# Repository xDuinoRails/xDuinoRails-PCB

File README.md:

View this project on [CADLAB.io](https://cadlab.io/project/28657).

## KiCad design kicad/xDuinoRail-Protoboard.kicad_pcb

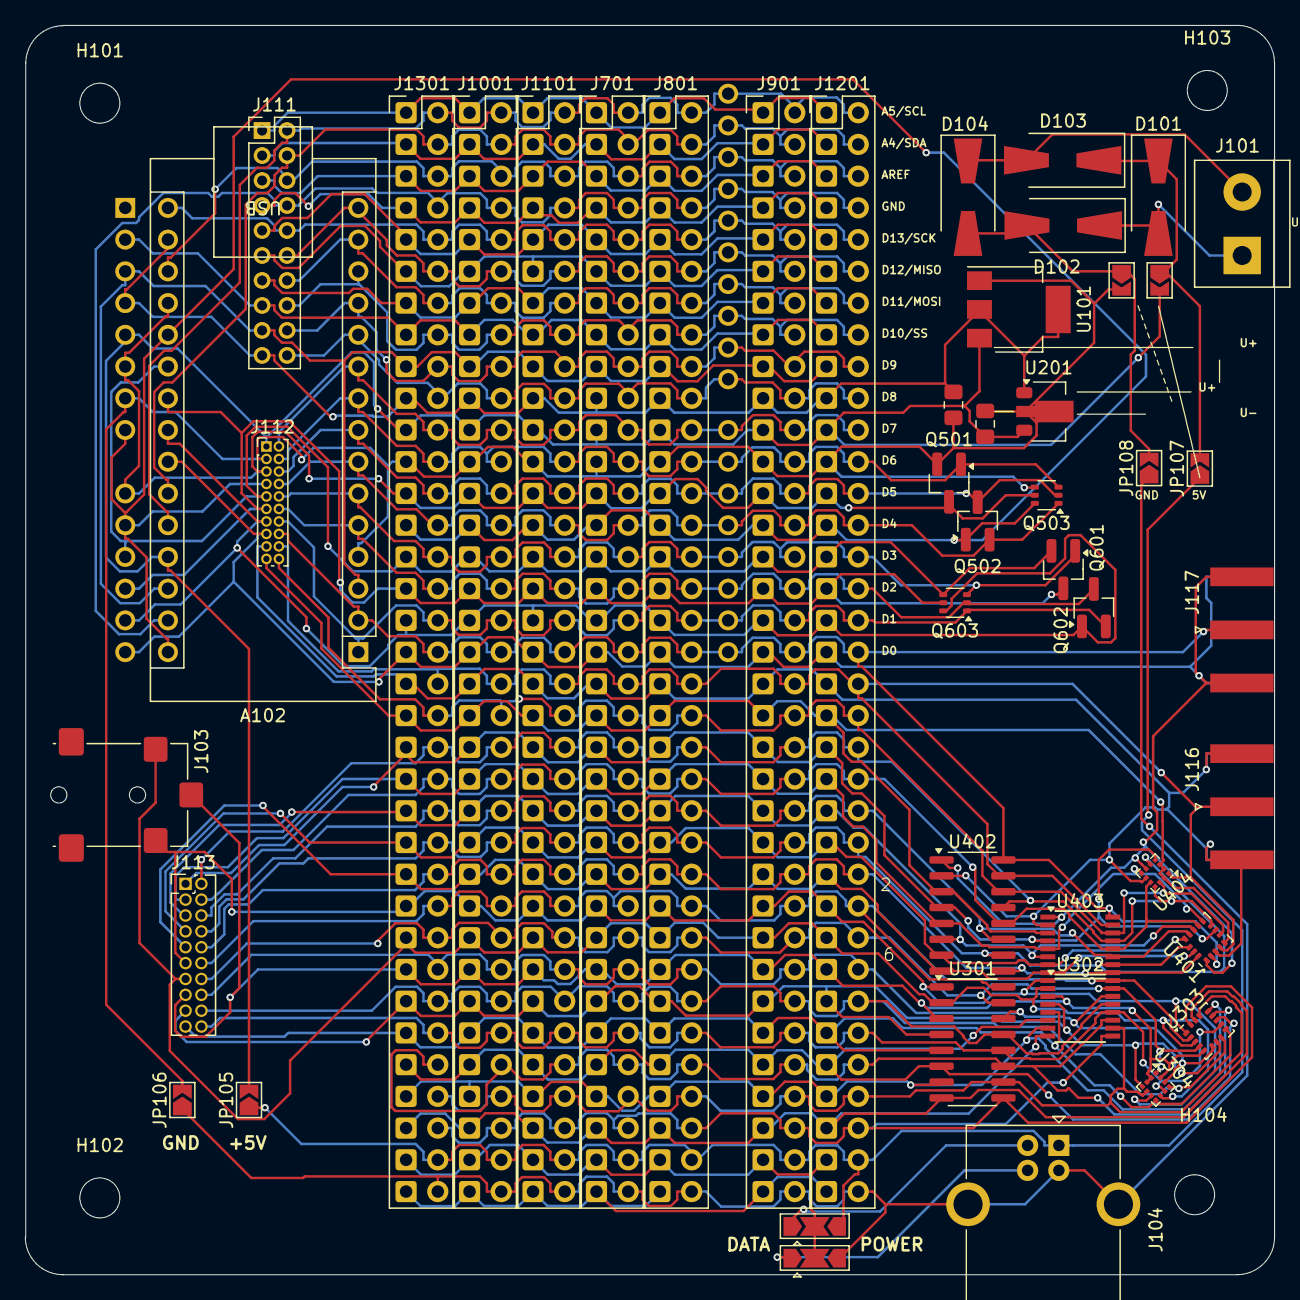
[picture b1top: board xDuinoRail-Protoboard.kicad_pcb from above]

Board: 2 copper layers, 100.0 x 100.0 mm, 51 parts (1 on the bottom side), 76 nets.

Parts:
A101: Arduino_UNO_R3
A102: Arduino_Nano_v3.x; Arduino_Nano
C201: 1uF; C_0805_2012Metric_Pad1.18x1.45mm_HandSolder
C202: 47uF; C_0805_2012Metric_Pad1.18x1.45mm_HandSolder
D101, D102, D103, D104: D; D_SMA-SMB_Universal_Handsoldering
H101, H102, H103, H104: MountingHole; MountingHole_3.2mm_M3
J101: Screw_Terminal_01x02; TerminalBlock_bornier-2_P5.08mm
J103: AudioJack3_Ground; Jack_3.5mm_Lumberg_1503_03_Horizontal
J104: USB_B; USB_B_OST_USB-B1HSxx_Horizontal
J111: Conn_02x10_Counter_Clockwise; PinHeader_2x10_P2.00mm_Vertical
J112: Conn_02x10_Counter_Clockwise; PinHeader_2x10_P1.00mm_Vertical
J113: Conn_02x10_Counter_Clockwise; PinHeader_2x10_P1.27mm_Vertical
J116, J117: Conn_Coaxial_Small; SMA_Amphenol_132289_EdgeMount
J701, J801, J901, J1001, J1101, J1201, J1301: Conn_02x35_Counter_Clockwise; PinHeader_2x35_P2.54mm_Vertical_Proto
JP103, JP104, JP105, JP106, JP107, JP108: SolderJumper_2_Open; SolderJumper-2_P1.3mm_Open_TrianglePad1.0x1.5mm
JP109, JP110: SolderJumper_3_Open; SolderJumper-3_P2.0mm_Open_TrianglePad1.0x1.5mm
Q501, Q502, Q601, Q602: 2N7002; SOT-23_Handsoldering
Q503, Q603: BC857BS; SOT-363_SC-70-6
U101: AMS1117-3.3; SOT-223-3_TabPin2
U201: HT7533-1; SOT-89-3
U301, U402: ULN2003; SOIC-16_3.9x9.9mm_P1.27mm
U302, U403: ULN2003; SSOP-16_3.9x4.9mm_P0.635mm
U303, U401: LIS3DH; LGA-16_3x3mm_P0.5mm_LayoutBorder3x5y
U304, U404: LIS3MDL; LGA-12_2x2mm_P0.5mm

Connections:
/AC0: D103.2 (A), D104.1 (K), J101.2
/AC1: D101.2 (A), D102.1 (K), J101.1
/Dm: J104.2 (D-), JP109.1 (A)
/Dp: J104.3 (D+), JP110.1 (A)
/L1: J111.1, J701.1, J801.1, J901.1, J1001.1, J1101.1, J1201.1, J1301.1
/L2: A101.32 (SCL/A5), A102.26 (A7), J111.2, J701.2, J801.2, J901.2, J1001.2, J1101.2, J1201.2, J1301.2
/L3: J111.3, J701.3, J801.3, J901.3, J1001.3, J1101.3, J1201.3, J1301.3
/L4: A101.31 (SDA/A4), A102.25 (A6), J111.4, J701.4, J801.4, J901.4, J1001.4, J1101.4, J1201.4, J1301.4
/L5: J111.5, J701.5, J801.5, J901.5, J1001.5, J1101.5, J1201.5, J1301.5
/L6: A101.30 (AREF), A102.18 (AREF), J111.6, J701.6, J801.6, J901.6, J1001.6, J1101.6, J1201.6, J1301.6
/L7: J111.7, J701.7, J801.7, J901.7, J1001.7, J1101.7, J1201.7, J1301.7
/L8: A101.29 (GND), A102.29 (GND), J111.8, J701.8, J801.8, J901.8, J1001.8, J1101.8, J1201.8, J1301.8
/L9: J111.9, J701.9, J801.9, J901.9, J1001.9, J1101.9, J1201.9, J1301.9
/L10: A101.28 (D13), A102.16 (D13), J111.10, J701.10, J801.10, J901.10, J1001.10, J1101.10, J1201.10, J1301.10
/L11: J111.11, J701.11, J801.11, J901.11, J1001.11, J1101.11, J1201.11, J1301.11
/L12: A101.27 (D12), A102.15 (D12), J111.12, J701.12, J801.12, J901.12, J1001.12, J1101.12, J1201.12, J1301.12
/L13: J111.13, J701.13, J801.13, J901.13, J1001.13, J1101.13, J1201.13, J1301.13
/L14: A101.26 (D11), A102.14 (D11), J111.14, J701.14, J801.14, J901.14, J1001.14, J1101.14, J1201.14, J1301.14
/L15: A101.2 (IOREF), J111.15, J701.15, J801.15, J901.15, J1001.15, J1101.15, J1201.15, J1301.15
/L16: A101.25 (D10), A102.13 (D10), J111.16, J701.16, J801.16, J901.16, J1001.16, J1101.16, J1201.16, J1301.16
/L17: A101.3 (~RESET), A102.3 (~RESET), A102.28 (~RESET), J111.17, J701.17, J801.17, J901.17, J1001.17, J1101.17, J1201.17, J1301.17
/L18: A101.24 (D9), A102.12 (D9), J111.18, J701.18, J801.18, J901.18, J1001.18, J1101.18, J1201.18, J1301.18
/L19: A101.4 (3V3), A102.17 (3V3), C202.1, J111.19, J701.19, J801.19, J901.19, J1001.19, J1101.19, J1201.19, J1301.19, U101.2 (VO), U201.1 (OUT)
/L20: A101.23 (D8), A102.11 (D8), J111.20, J701.20, J801.20, J901.20, J1001.20, J1101.20, J1201.20, J1301.20
/L21: A101.5 (+5V), A102.27 (+5V), C201.1, J112.1, J701.21, J801.21, J901.21, J1001.21, J1101.21, J1201.21, J1301.21, JP103.2 (B), JP105.2 (B), U101.3 (VI), U201.3 (IN)
/L22: A101.22 (D7), A102.10 (D7), J112.2, J701.22, J801.22, J901.22, J1001.22, J1101.22, J1201.22, J1301.22
/L24: A101.21 (D6), A102.9 (D6), J112.4, J701.24, J801.24, J901.24, J1001.24, J1101.24, J1201.24, J1301.24, Q501.1 (G), Q503.3 (C2)
/L25: A101.6 (GND), A101.9 (A0), A102.19 (A0), J112.5, J701.25, J801.25, J901.25, J1001.25, J1101.25, J1201.25, J1301.25, Q501.3 (D), Q503.5 (B2)
/L26: A101.20 (D5), A102.8 (D5), J112.6, J701.26, J801.26, J901.26, J1001.26, J1101.26, J1201.26, J1301.26, Q502.3 (D), Q503.2 (B1)
/L27: A101.8 (VIN), A101.10 (A1), A102.20 (A1), A102.30 (VIN), J112.7, J701.27, J801.27, J901.27, J1001.27, J1101.27, J1201.27, J1301.27, Q502.1 (G), Q503.6 (C1)
/L28: A101.19 (D4), A102.7 (D4), J112.8, J701.28, J801.28, J901.28, J1001.28, J1101.28, J1201.28, J1301.28, Q502.2 (S), Q503.1 (E1)
/L29: A101.11 (A2), A102.21 (A2), J112.9, J701.29, J801.29, J901.29, J1001.29, J1101.29, J1201.29, J1301.29, Q601.2 (S), Q603.4 (E2)
/L30: A101.18 (D3), A102.6 (D3), J112.10, J701.30, J801.30, J901.30, J1001.30, J1101.30, J1201.30, J1301.30, Q601.1 (G), Q603.3 (C2)
/L31: A101.12 (A3), A102.22 (A3), J112.11, J701.31, J801.31, J901.31, J1001.31, J1101.31, J1201.31, J1301.31, Q601.3 (D), Q603.5 (B2)
/L32: A101.17 (D2), A102.5 (D2), J112.12, J701.32, J801.32, J901.32, J1001.32, J1101.32, J1201.32, J1301.32, Q602.3 (D), Q603.2 (B1)
/L33: A101.13 (SDA/A4), A102.23 (A4), J112.13, J701.33, J801.33, J901.33, J1001.33, J1101.33, J1201.33, J1301.33, Q602.1 (G), Q603.6 (C1)
/L34: A101.16 (D1/TX), A102.1 (D1/TX), J112.14, J701.34, J801.34, J901.34, J1001.34, J1101.34, J1201.34, J1301.34, Q602.2 (S), Q603.1 (E1)
/L35: A101.14 (SCL/A5), A102.24 (A5), J112.15, J117.2 (Ext), J701.35, J801.35, J901.35, J1001.35, J1101.35, J1201.35, J1301.35, U401.1 (VDD_IO), U402.1 (I1), U403.1 (I1), U404.6 (Vdd_IO)
/L36: A101.15 (D0/RX), A102.2 (D0/RX), J112.16, J117.1 (In), J701.36, J801.36, J901.36, J1001.36, J1101.36, J1201.36, J1301.36, U401.2 (NC), U402.16 (O1), U403.16 (O1)
/L37: J112.17, J116.2 (Ext), J701.37, J801.37, J901.37, J1001.37, J1101.37, J1201.37, J1301.37, U401.3 (NC), U402.2 (I2), U403.2 (I2), U404.8 (DRDY)
/L38: J112.18, J116.1 (In), J701.38, J801.38, J901.38, J1001.38, J1101.38, J1201.38, J1301.38, U401.4 (SCL/SPC), U402.15 (O2), U403.15 (O2), U404.1 (SCL/SPC)
/L39: J112.19, J701.39, J801.39, J901.39, J1001.39, J1101.39, J1201.39, J1301.39, U401.5 (GND), U402.3 (I3), U403.3 (I3), U404.2 (GND), U404.3 (GND), U404.12 (GND)
/L40: J112.20, J701.40, J801.40, J901.40, J1001.40, J1101.40, J1201.40, J1301.40, U401.6 (SDA/SDI/SDO), U402.14 (O3), U403.14 (O3), U404.11 (SDA/SDI/SDO)
/L41: J113.1, J701.41, J801.41, J901.41, J1001.41, J1101.41, J1201.41, J1301.41, U401.7 (SDO/SA0), U402.4 (I4), U403.4 (I4), U404.4 (C1)
/L42: J113.2, J701.42, J801.42, J901.42, J1001.42, J1101.42, J1201.42, J1301.42, U401.8 (CS), U402.13 (O4), U403.13 (O4), U404.10 (~CS)
/L43: J113.3, J701.43, J801.43, J901.43, J1001.43, J1101.43, J1201.43, J1301.43, U401.9 (INT2), U402.5 (I5), U403.5 (I5), U404.7 (INT)
/L44: J113.4, J701.44, J801.44, J901.44, J1001.44, J1101.44, J1201.44, J1301.44, U401.10 (GND), U402.12 (O5), U403.12 (O5), U404.9 (SDO/SA1)
/L45: J113.5, J701.45, J801.45, J901.45, J1001.45, J1101.45, J1201.45, J1301.45, U401.11 (INT1), U402.6 (I6), U403.6 (I6)
/L46: J113.6, J701.46, J801.46, J901.46, J1001.46, J1101.46, J1201.46, J1301.46, U401.12 (GND), U402.11 (O6), U403.11 (O6)
/L47: J113.7, J701.47, J801.47, J901.47, J1001.47, J1101.47, J1201.47, J1301.47, U401.13 (ADC3), U402.7 (I7), U403.7 (I7)
/L48: J113.8, J701.48, J801.48, J901.48, J1001.48, J1101.48, J1201.48, J1301.48, U401.14 (VDD), U402.10 (O7), U403.10 (O7), U404.5 (Vdd)
/L49: J113.9, J701.49, J801.49, J901.49, J1001.49, J1101.49, J1201.49, J1301.49, U401.15 (ADC2), U402.8 (GND), U403.8 (GND)
/L50: J113.10, J701.50, J801.50, J901.50, J1001.50, J1101.50, J1201.50, J1301.50, U401.16 (ADC1), U402.9 (COM), U403.9 (COM)
/L51: J103.S, J113.11, J701.51, J801.51, J901.51, J1001.51, J1101.51, J1201.51, J1301.51, U301.1 (I1), U302.1 (I1), U303.1 (VDD_IO), U304.6 (Vdd_IO)
/L52: J113.12, J701.52, J801.52, J901.52, J1001.52, J1101.52, J1201.52, J1301.52, U301.16 (O1), U302.16 (O1), U303.2 (NC)
/L53: J103.R, J113.13, J701.53, J801.53, J901.53, J1001.53, J1101.53, J1201.53, J1301.53, U301.2 (I2), U302.2 (I2), U303.3 (NC), U304.8 (DRDY)
/L54: J113.14, J701.54, J801.54, J901.54, J1001.54, J1101.54, J1201.54, J1301.54, U301.15 (O2), U302.15 (O2), U303.4 (SCL/SPC), U304.1 (SCL/SPC)
/L55: J103.T, J113.15, J701.55, J801.55, J901.55, J1001.55, J1101.55, J1201.55, J1301.55, U301.3 (I3), U302.3 (I3), U303.5 (GND), U304.2 (GND), U304.3 (GND), U304.12 (GND)
/L56: J113.16, J701.56, J801.56, J901.56, J1001.56, J1101.56, J1201.56, J1301.56, U301.14 (O3), U302.14 (O3), U303.6 (SDA/SDI/SDO), U304.11 (SDA/SDI/SDO)
/L57: J113.17, J701.57, J801.57, J901.57, J1001.57, J1101.57, J1201.57, J1301.57, U301.4 (I4), U302.4 (I4), U303.7 (SDO/SA0), U304.4 (C1)
/L58: J113.18, J701.58, J801.58, J901.58, J1001.58, J1101.58, J1201.58, J1301.58, U301.13 (O4), U302.13 (O4), U303.8 (CS), U304.10 (~CS)
/L59: J113.19, J701.59, J801.59, J901.59, J1001.59, J1101.59, J1201.59, J1301.59, U301.5 (I5), U302.5 (I5), U303.9 (INT2), U304.7 (INT)
/L60: J113.20, J701.60, J801.60, J901.60, J1001.60, J1101.60, J1201.60, J1301.60, U301.12 (O5), U302.12 (O5), U303.10 (GND), U304.9 (SDO/SA1)
/L61: J701.61, J801.61, J901.61, J1001.61, J1101.61, J1201.61, J1301.61, U301.6 (I6), U302.6 (I6), U303.11 (INT1)
/L62: J701.62, J801.62, J901.62, J1001.62, J1101.62, J1201.62, J1301.62, U301.11 (O6), U302.11 (O6), U303.12 (GND)
/L63: J701.63, J801.63, J901.63, J1001.63, J1101.63, J1201.63, J1301.63, U301.7 (I7), U302.7 (I7), U303.13 (ADC3)
/L64: J701.64, J801.64, J901.64, J1001.64, J1101.64, J1201.64, J1301.64, U301.10 (O7), U302.10 (O7), U303.14 (VDD), U304.5 (Vdd)
/L65: J701.65, J801.65, J901.65, J1001.65, J1101.65, J1201.65, J1301.65, U301.8 (GND), U302.8 (GND), U303.15 (ADC2)
/L66: J701.66, J801.66, J901.66, J1001.66, J1101.66, J1201.66, J1301.66, U301.9 (COM), U302.9 (COM), U303.16 (ADC1)
/L67: J701.67, J801.67, J901.67, J1001.67, J1101.67, J1201.67, J1301.67, JP109.2 (C), JP110.2 (C)
/L68: J104.1 (VBUS), J701.68, J801.68, J901.68, J1001.68, J1101.68, J1201.68, J1301.68, JP105.1 (A), JP107.1 (A), JP109.3 (B)
/L69: J701.69, J801.69, J901.69, J1001.69, J1101.69, J1201.69, J1301.69
/L70: J104.4 (GND), J104.5 (Shield), J701.70, J801.70, J901.70, J1001.70, J1101.70, J1201.70, J1301.70, JP106.1 (A), JP108.1 (A), JP110.3 (B)
/U+: D101.1 (K), D103.1 (K), JP103.1 (A), JP107.2 (B)
/U-: D102.2 (A), D104.2 (A), JP104.1 (A), JP108.2 (B)
GND: A101.7 (GND), A102.4 (GND), C201.2, C202.2, J112.3, J701.23, J801.23, J901.23, J1001.23, J1101.23, J1201.23, J1301.23, JP104.2 (B), JP106.2 (B), Q501.2 (S), Q503.4 (E2), U101.1 (GND), U201.2 (GND)

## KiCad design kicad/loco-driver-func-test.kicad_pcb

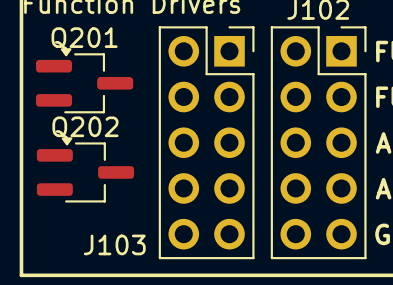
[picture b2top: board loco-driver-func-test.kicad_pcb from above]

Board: 2 copper layers, 4 parts (0 on the bottom side), 5 nets, no tracks yet.

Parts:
J102, J103: Conn_02x05_Odd_Even; PinSocket_2x05_P2.54mm_Vertical
Q201, Q202: AO3400A; SOT-23W_Handsoldering

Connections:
/J_AMP_FUNC0: J102.6, J103.5, J103.6, Q201.3 (D)
/J_AMP_FUNC1: J102.8, J103.7, J103.8, Q202.3 (D)
/J_FUNC0: J102.2, J103.1, J103.2, Q201.1 (G)
/J_FUNC1: J102.4, J103.3, J103.4, Q202.1 (G)
GND: J102.10, J103.9, J103.10, Q201.2 (S), Q202.2 (S)

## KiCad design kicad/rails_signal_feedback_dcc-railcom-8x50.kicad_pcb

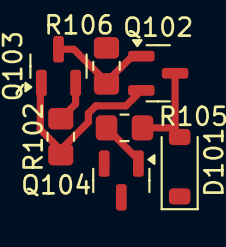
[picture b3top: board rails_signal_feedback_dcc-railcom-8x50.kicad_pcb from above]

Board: 2 copper layers, 7 parts (0 on the bottom side), 5 nets.

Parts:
D101: 1N5819W; D_SOD-123
Q102, Q103: S8550; 8x50_SOT-23
Q104: S8050; 8x50_SOT-23
R102: 20R; R_0805_2012Metric_Pad1.20x1.40mm_HandSolder
R105, R106: 10k; R_0805_2012Metric_Pad1.20x1.40mm_HandSolder

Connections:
/+3V3: Q103.1 (E), R102.2
/RC_CURR: Q102.1 (E), Q103.2 (B), R102.1
/RC_DATA_IN: Q102.2 (B), Q103.3 (C), R106.1
/RC_SIGNAL: D101.2 (A), Q102.3 (C), R105.1
/_TST_RC_ON_OFF: Q104.2 (B), R105.2

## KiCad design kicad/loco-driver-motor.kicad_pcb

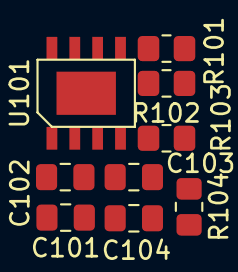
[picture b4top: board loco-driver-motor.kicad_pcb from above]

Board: 2 copper layers, 9 parts (0 on the bottom side), 7 nets, no tracks yet.

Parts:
C101, C103: 10uF; C_0805_2012Metric_Pad1.18x1.45mm_HandSolder
C102, C104: 100nF; C_0805_2012Metric_Pad1.18x1.45mm_HandSolder
R101, R103: 6k8; R_0805_2012Metric_Pad1.20x1.40mm_HandSolder
R102, R104: 1k; R_0805_2012Metric_Pad1.20x1.40mm_HandSolder
U101: BDR6133

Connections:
/+3V3: C101.1, C102.1, U101.2 (VCC)
/AMP_MOTOR0: R103.2, U101.4 (OUTA)
/AMP_MOTOR1: R101.2, U101.5 (OUTB)
/EMF_MOTOR0: R103.1, R104.1
/EMF_MOTOR1: R101.1, R102.1
/U+: C103.1, C104.1, U101.3 (VM)
GND: C101.2, C102.2, C103.2, C104.2, R102.2, R104.2, U101.1 (GND), U101.9 (PGND)

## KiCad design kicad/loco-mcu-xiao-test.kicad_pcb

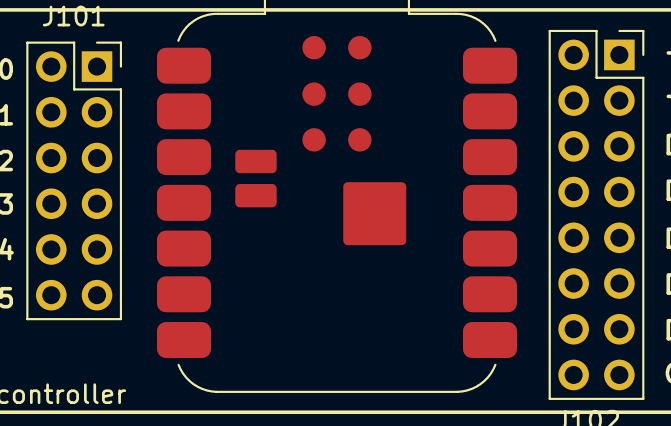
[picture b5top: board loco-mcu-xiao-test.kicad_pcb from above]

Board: 2 copper layers, 3 parts (0 on the bottom side), 14 nets, no tracks yet.

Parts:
J101: Conn_02x06_Odd_Even; PinSocket_2x06_P2.54mm_Vertical
J102: Conn_02x08_Odd_Even; PinSocket_2x08_P2.54mm_Vertical
U201: MOUDLE-SEEEDUINO-XIAO-ESP32C3; MCU_Seeed_ESP32C3

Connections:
+3V3: J102.4, U201.14 (5V)
+5V: J102.2, U201.12 (3V3)
/J_AUDIO: J101.1, U201.1 (A0)
/J_BACK_EMF0: J101.3, U201.2 (A1)
/J_BACK_EMF1: J101.5, U201.3 (A2)
/J_DECODER: J101.7, U201.4 (A3)
/J_FUNC0: J102.10, U201.9 (A8_SCK)
/J_FUNC1: J102.12, U201.8 (A7_RX)
/J_GND: J102.16, U201.13 (GND)
/J_I2C.SCL: J101.11, U201.6 (A5_SCL)
/J_I2C.SDA: J101.9, U201.5 (A4_SDA)
/J_MOTOR0: J102.6, U201.11 (A10_MOSI)
/J_MOTOR1: J102.8, U201.10 (A9_MISO)
/J_RAILCOM: J102.14, U201.7 (A6_TX)

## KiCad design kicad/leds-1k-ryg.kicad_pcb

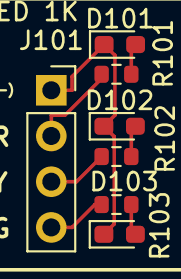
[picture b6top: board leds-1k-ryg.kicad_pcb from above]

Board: 2 copper layers, 7 parts (0 on the bottom side), 7 nets.

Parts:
D101: LED_RED; LED_0603_1608Metric_Pad1.05x0.95mm_HandSolder
D102: LED_YELLOW; LED_0603_1608Metric_Pad1.05x0.95mm_HandSolder
D103: LED_GREEN; LED_0603_1608Metric_Pad1.05x0.95mm_HandSolder
J101: Conn_01x04; PinSocket_1x04_P2.54mm_Vertical
R101, R102, R103: 1k; R_0603_1608Metric

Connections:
/GND: D101.1 (K), D102.1 (K), D103.1 (K), J101.1
/LED1: J101.2, R101.1
/LED2: J101.3, R102.1
/LED3: J101.4, R103.1
unnamed: D101.2 (A), R101.2
unnamed: D102.2 (A), R102.2
unnamed: D103.2 (A), R103.2

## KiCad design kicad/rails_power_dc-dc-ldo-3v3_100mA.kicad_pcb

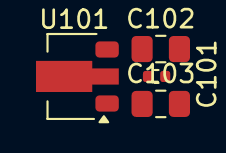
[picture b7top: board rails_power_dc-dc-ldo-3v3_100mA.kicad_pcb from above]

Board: 2 copper layers, 4 parts (0 on the bottom side), 3 nets, no tracks yet.

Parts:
C101: 1u; C_0402_1005Metric
C102, C103: 47uF; C_0805_2012Metric_Pad1.18x1.45mm_HandSolder
U101: HT75xx-1-SOT89; SOT-89-3

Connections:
/+3V3: C102.1, U101.3 (VOUT)
/GND: C101.2, C102.2, C103.2, U101.1 (GND)
/U+: C101.1, C103.1, U101.2 (VIN)

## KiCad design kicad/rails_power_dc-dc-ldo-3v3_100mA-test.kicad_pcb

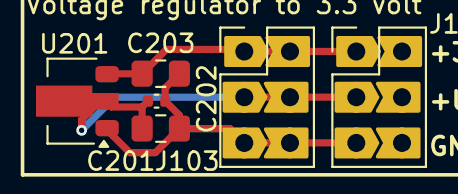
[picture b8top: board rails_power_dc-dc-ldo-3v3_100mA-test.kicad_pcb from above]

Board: 2 copper layers, 6 parts (0 on the bottom side), 3 nets.

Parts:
C201, C203: 47uF; C_0805_2012Metric_Pad1.18x1.45mm_HandSolder
C202: 1u; C_0402_1005Metric
J101, J103: Conn_02x03_Odd_Even; PinHeaderJP_2x03_P2.54mm_Vertical
U201: HT75xx-1-SOT89; SOT-89-3

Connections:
/J_3v3: C203.1, J101.1, J103.1, J103.2, U201.3 (VOUT)
/J_GND: C201.2, C202.2, C203.2, J101.5, J103.5, J103.6, U201.1 (GND)
/J_U+: C201.1, C202.1, J101.3, J103.3, J103.4, U201.2 (VIN)

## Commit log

2024-11-05 Add - Initial schematics
2024-11-05 Add - PDF for ease of read
2024-11-10 Backlink to CADLAB.io has been added.
